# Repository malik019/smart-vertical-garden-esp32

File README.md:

# 🌱 Smart Vertical Garden — ESP32-C6 Hydroponics Controller

An automated, modular **Hydroponics Grow Tower** controller powered by an **ESP32-C6 (`ESP32-C6-DevKitC-1`)**. The system autonomously monitors environmental conditions, regulates lighting and irrigation schedules, protects against dry-running pump faults, provides a local asynchronous web interface with OTA updates, and streams real-time telemetry to **MQTT, Telegraf, InfluxDB, and Grafana**.

---

## 🏗️ System Architecture

The project is structured into five decoupled layers:

### 1. Sensors & Measurements (`firmware/` — `sensors.cpp`)
* **Ambient Temperature:** Read every 5 seconds via a **BMP280** sensor over I2C (`GPIO 4` / `GPIO 5`).
* **Reservoir Water Level:** Measured with an **HC-SR04** ultrasonic sensor (`GPIO 6` / `GPIO 7`, protected by a voltage divider on the Echo pin to step 5V down to 3.3V), calibrated between `10 cm = 100%` and `50 cm = 0%`.
* **Water Temperature:** Currently simulated in software and hardware-ready for a 1-Wire **DS18B20** probe (`GPIO 10`).

### 2. Automation & Fail-Safe Protection (`firmware/` — `control.cpp`)
* **NTP Time Synchronization:** Syncs internal time over WiFi via NTP to drive daily schedules accurately.
* **PWM Grow Light Dimming:** Calculates LED brightness (`0–255`) every second via PWM (`GPIO 3`), featuring smooth sunrise and sunset fade windows.
* **Irrigation Cycle & Dry-Run Protection:** Controls the water pump (`GPIO 2`) on a configurable timer. If the reservoir water level drops below the safety threshold, the fail-safe immediately shuts off the pump and triggers a `CRITICAL_LOW_WATER` alarm state.

### 3. Local Web Interface, LittleFS & OTA (`firmware/` — `web_server.cpp`)
* **Non-Hardcoded Web Assets:** Hosted by `ESPAsyncWebServer` with all HTML, CSS, and JavaScript files served directly from internal **LittleFS** flash storage.
* **Live Control & File Management:** View live sensor readings, manually override the pump or LED dimmer, adjust schedules, and perform wireless **Over-The-Air (OTA)** firmware and filesystem updates.
* **JSON Configuration Persistence:** All WiFi credentials and system parameters are stored in `config.json` on LittleFS so settings survive reboots and power loss.

### 4. Power Electronics & PCB Design (`hardware/`)
* **Isolated 12V Switching:** Two **AO3400A Logic-Level MOSFETs** (with `10kΩ` gate pull-down resistors) isolate the 3.3V ESP32-C6 logic from the 12V LED grow lights and 12V water pump.
* **Inductive Kickback Protection:** A **1N914** flyback diode is placed across the pump terminals to suppress voltage spikes.
* **KiCad Hardware Files:** Full schematic, PCB layout, 3D STEP models, and fabrication plots are available in the `hardware/` directory.

### 5. Telemetry & Grafana Monitoring Dashboard
* **Telemetry Pipeline:** `ESP32-C6` → `Mosquitto MQTT (hydro_tower/001/telemetry)` → `Telegraf` → `InfluxDB` → `Grafana`.
* **Real-Time Visualization:**
  * **Gauges:** Water level (`%`), ambient temperature (`°C`), water temperature (`°C`), and LED PWM brightness (`0–255`).
  * **Status Panels:** Live `pump_status` (`ON` / `OFF`) and `alarm` state (`NONE` / `CRITICAL_LOW_WATER`).
  * **Time-Series History:** Historical graphs tracking reservoir water level and temperature trends over time.

---

## 📌 Hardware Pinout (`ESP32-C6-DevKitC-1`)

| Peripheral | Signal / Bus | ESP32-C6 GPIO | Notes |
| :--- | :--- | :--- | :--- |
| **Water Pump (12V)** | MOSFET Gate (PWM/Digital) | `GPIO 2` | AO3400A + 10kΩ pull-down + 1N914 flyback diode |
| **LED Grow Lights (12V)** | MOSFET Gate (PWM) | `GPIO 3` | AO3400A + 10kΩ pull-down, smooth fade window |
| **BMP280 Sensor** | I2C SDA / SCL | `GPIO 4` / `GPIO 5` | 3.3V ambient temperature |
| **HC-SR04 Ultrasonic** | Trigger / Echo | `GPIO 6` / `GPIO 7` | Voltage divider on Echo (`5V -> 3.3V`) |
| **DS18B20 Probe** | 1-Wire Data | `GPIO 10` | Reserved for physical water temperature probe |

---

## 📡 MQTT Telemetry Payload Example

Published periodically to `hydro_tower/001/telemetry`:

```json
{
  "room_temp": 18.78,
  "room_humidity": 52,
  "water_temp": 13.4,
  "water_level": 73,
  "pump_status": "ON",
  "light_brightness": 71,
  "alarm": "NONE"
}
```

---

## 📂 Repository Structure

```text
smart-vertical-garden-esp32/
├── docs/          # Project documentation, diagrams, and dashboard screenshots
├── firmware/      # ESP32-C6 C++ source code (sensors, control, web server) & LittleFS data/
├── hardware/      # KiCad schematics, PCB layout, 3D models, and Gerber/PDF plots
└── README.md      # Project overview and setup guide
```

---

## 🚀 Quick Start

1. **Firmware & LittleFS:** Open `firmware/` in Arduino IDE or PlatformIO (target board: `ESP32C6 Dev Module`), upload the LittleFS filesystem (`data/`), and flash the firmware.
2. **OOTB WiFi Setup:** On first boot without saved credentials, connect to the ESP32-C6 WiFi Manager access point to configure your WiFi network and MQTT settings (saved automatically to `config.json`).
3. **Monitoring Stack:** Configure Mosquitto, Telegraf (`json_string_fields = ["pump_status", "alarm"]`), InfluxDB, and import the Grafana dashboard from `docs/`.

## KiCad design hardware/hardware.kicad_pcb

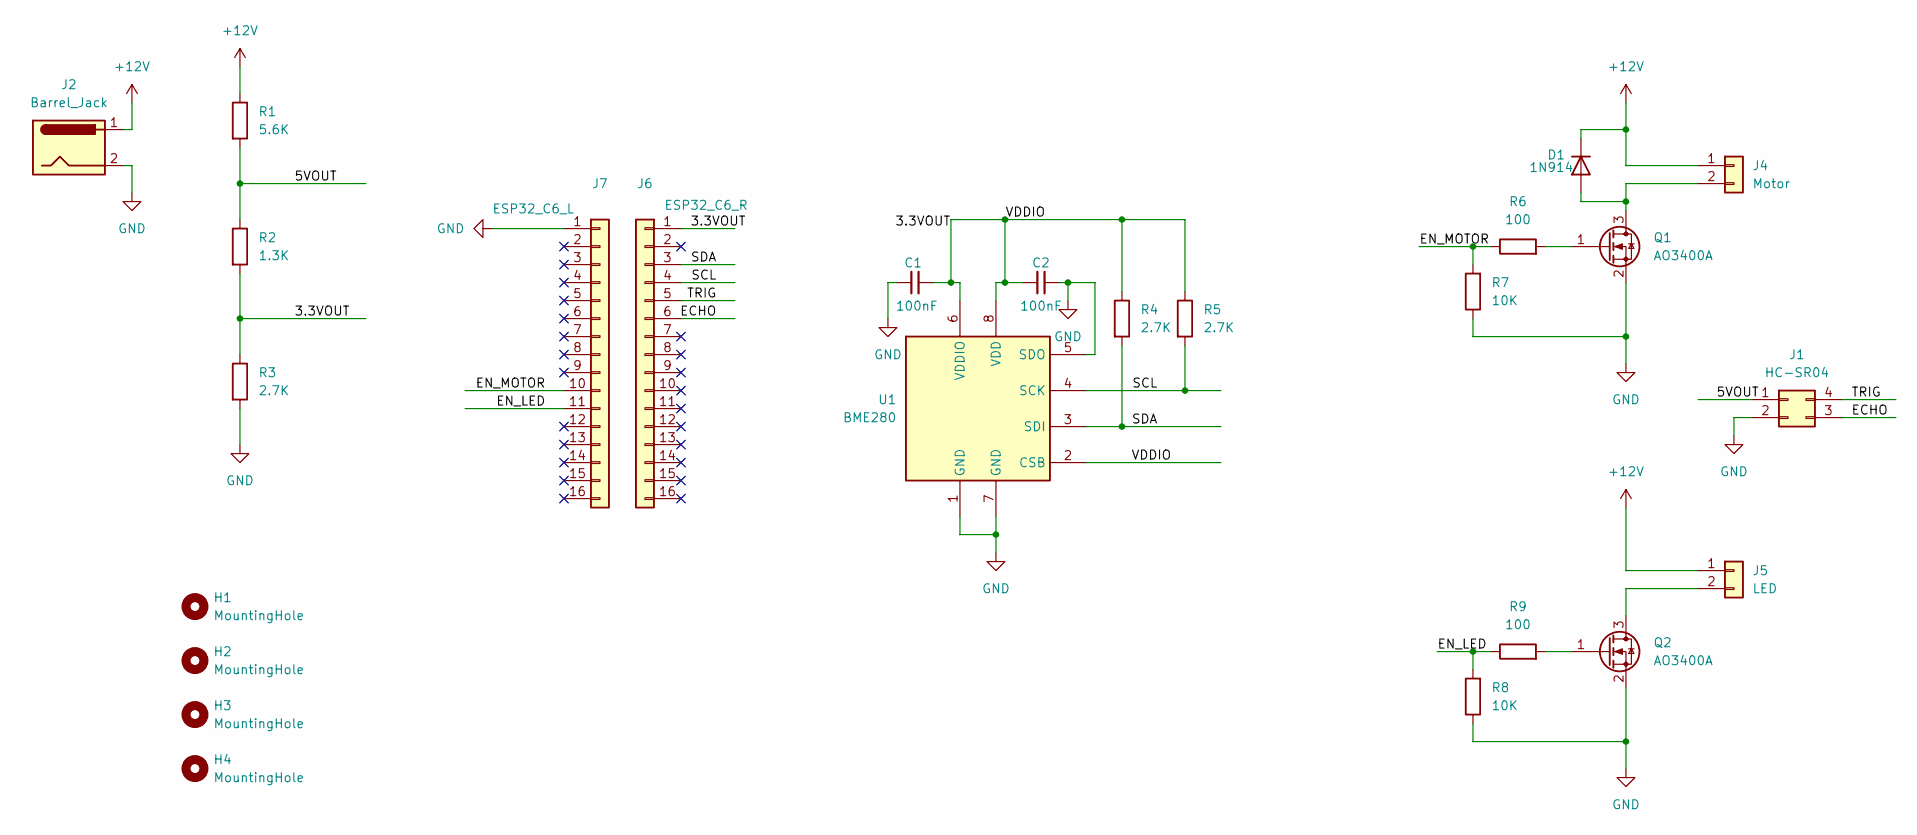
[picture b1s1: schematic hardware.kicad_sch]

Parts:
C1, C2: 100nF; C_Disc_D3.0mm_W1.6mm_P2.50mm
D1: 1N914; D_DO-35_SOD27_P7.62mm_Horizontal
H1, H2, H3, H4: MountingHole; MountingHole_2.2mm_M2
J1: HC-SR04; PinSocket_1x04_P2.54mm_Horizontal
J2: Barrel_Jack; BarrelJack_SwitchcraftConxall_RAPC10U_Horizontal
J4: Motor; PinHeader_1x02_P2.54mm_Vertical
J5: LED; PinHeader_1x02_P2.54mm_Vertical
J6: ESP32_C6_R; PinSocket_1x16_P2.54mm_Vertical
J7: ESP32_C6_L; PinSocket_1x16_P2.54mm_Vertical
Q1, Q2: AO3400A; SOT-23
R1: 5.6K; R_Axial_DIN0207_L6.3mm_D2.5mm_P7.62mm_Horizontal
R2: 1.3K; R_Axial_DIN0207_L6.3mm_D2.5mm_P7.62mm_Horizontal
R3, R4, R5: 2.7K; R_Axial_DIN0207_L6.3mm_D2.5mm_P7.62mm_Horizontal
R6, R9: 100; R_Axial_DIN0207_L6.3mm_D2.5mm_P7.62mm_Horizontal
R7, R8: 10K; R_Axial_DIN0207_L6.3mm_D2.5mm_P7.62mm_Horizontal
U1: BME280; Bosch_LGA-8_2.5x2.5mm_P0.65mm_ClockwisePinNumbering

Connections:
+12V: D1.1 (K), J2.1, J4.1, J5.1, R1.1
/3.3VOUT: C1.2, C2.1, J6.1, R2.2, R3.1, R4.1, R5.1, U1.2 (CSB), U1.6 (VDDIO), U1.8 (VDD)
/5VOUT: J1.1, R1.2, R2.1
/ECHO: J1.3, J6.6
/EN_LED: J7.11, R8.2, R9.1
/EN_MOTOR: J7.10, R6.1, R7.2
/SCL: J6.4, R5.2, U1.4 (SCK)
/SDA: J6.3, R4.2, U1.3 (SDI)
/TRIG: J1.4, J6.5
GND: C1.1, C2.2, J1.2, J2.2, J7.1, Q1.2 (S), Q2.2 (S), R3.2, R7.1, R8.1, U1.1 (GND), U1.5 (SDO), U1.7 (GND)
unnamed: D1.2 (A), J4.2, Q1.3 (D)
unnamed: J5.2, Q2.3 (D)
unnamed: Q1.1 (G), R6.2
unnamed: Q2.1 (G), R9.2

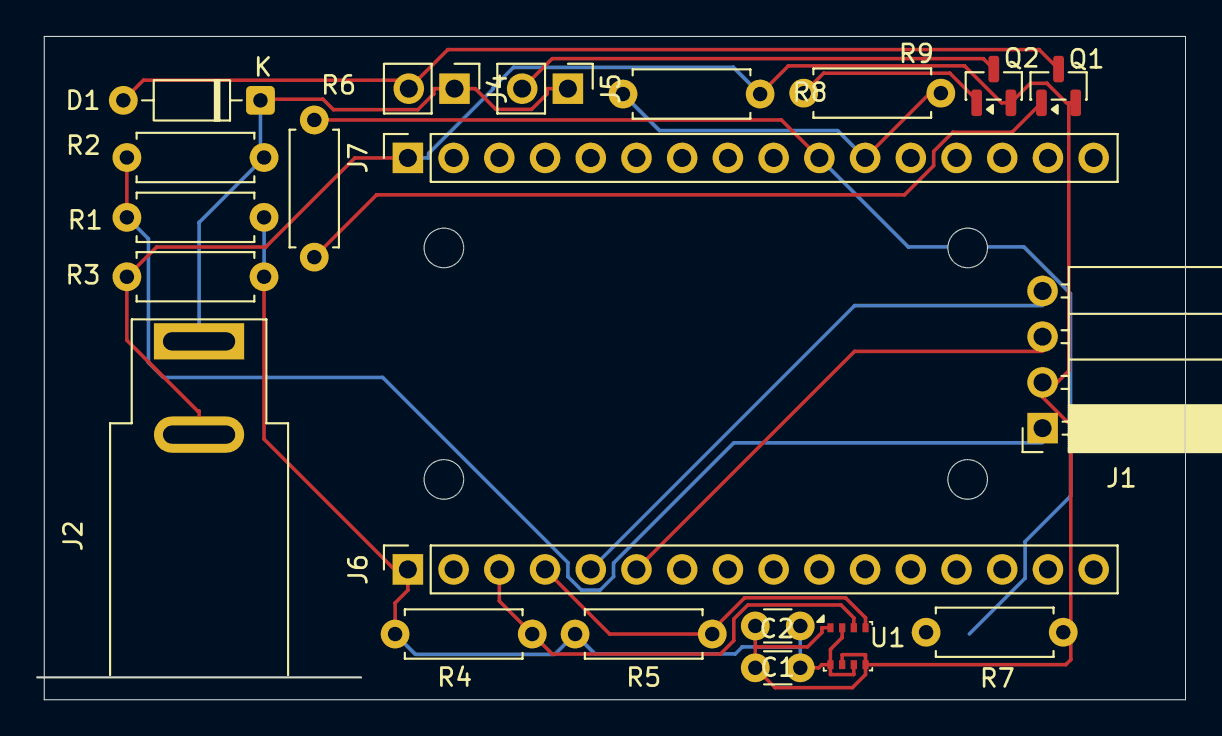
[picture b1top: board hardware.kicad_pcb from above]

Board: 2 copper layers, 63.4 x 36.8 mm, 25 parts (0 on the bottom side), 14 nets.

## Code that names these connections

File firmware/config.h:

#pragma once
#include <Arduino.h>

struct WifiConfig {
  String ssid = "";
  String password = "";
};

struct NtpConfig {
  String server = "pool.ntp.org";
  long gmt_offset = 3600;
  int daylight_offset = 3600;
};

struct LightingConfig {
  String start_time = "06:00";
  String end_time = "22:00";
  int fade_duration_min = 15;
};

struct IrrigationConfig {
  int on_duration_min = 5;
  int interval_min = 45;
};

struct ThresholdsConfig {
  float min_water_level_pct = 20.0;
  float max_water_temp_c = 26.0;
  float max_room_temp_c = 35.0;
};

struct MqttConfig {
  String broker = "://hivemq.com"; 
  int port = 1883;
  String user = "cobalt";          
  String password = "testmqtt";  
  String prefix = "hydro_tower/001";
  int interval_sec = 30;
};

// Global handles accessible by all modules
extern WifiConfig wifiCfg;
extern NtpConfig ntpCfg;
extern LightingConfig lightCfg;
extern IrrigationConfig irrCfg;
extern ThresholdsConfig threshCfg;
extern MqttConfig mqttCfg;

extern bool shouldSaveConfig;
extern String ledState;
extern float roomTemp, roomHumidity, waterTemp, waterLevelPct;
extern bool pumpState;
extern int currentLedBrightness;
extern String alarmState;

// Dynamic runtime system-override handles
extern bool manualPumpOverride;
extern unsigned long manualPumpTimeout;
extern bool manualLedOverride;
extern unsigned long manualLedTimeout;

// ESP32-C6-DevKitC-1 Pin Definitions (Safe non-strapping, non-USB GPIOs)
#define PIN_POMP            2   // Pump AO3400A MOSFET Gate (EN_MOTOR)
#define PIN_LED_PWM         3   // LED Grow Light PWM AO3400A Gate (EN_LED)

// ESP32-C6 Native I2C Pins (BMP280)
#define PIN_I2C_SDA         4   // ESP32-C6 Native SDA
#define PIN_I2C_SCL         5   // ESP32-C6 Native SCL

#define PIN_WATERTEMP       10  // 1-Wire Digital Pin (DS18B20)
#define PIN_LEVEL_TRIG      6   // HC-SR04 Ultrasonic Trigger
#define PIN_LEVEL_ECHO      7   // HC-SR04 Ultrasonic Echo (via 5.6k/1.3k divider)

// Function prototypes
void loadConfiguration();
void saveFullConfiguration();
String getFormattedTime();
